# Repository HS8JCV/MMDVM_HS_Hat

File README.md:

# MMDVM_HS_Hat (VHF)
MMDVM_HS Hat for the Raspberry Pi (Zero)

This project forked from https://github.com/mathisschmieder/MMDVM_HS_Hat

This project provides a Raspberry Pi Hat for the [MMDVM_HS Hotspot](https://github.com/juribeparada/MMDVM_HS). It was designed for the Raspberry Pi Zero, but should work on any other Pi with the Hat interface. 

The PCB is designed in KiCad and the necessary libraries are included. The supplied Gerber files can be used to order PCBs, for example at Elecrow or DirtyPCBs. The board's dimensions are 65x30mm.

You can order 3 beautiful, purple Revision 1.2.1(VHF) PCBs for $15 at [OSHPark](https://oshpark.com/shared_projects/D5eErGib)! 

## Revisions
If you want to know about other revisions ,Please goto  orginal repository https://github.com/mathisschmieder/MMDVM_HS_Hat
### Revision 1.2.1(VHF)
This Revision forked from revision 1.2 of https://github.com/mathisschmieder/MMDVM_HS_Hat

Detail
- Remove ceramic UHF antenna
- Add Inductor for External VCO
- Changed resistor and capacitor loop filter value
- Changed Lowpass filter circuit and value

## Customize schematic with Simulation Software

## Spectrum Result
Agilent N9340B with 20dB Attenuator

Spurious(2nd Harmonic)

50Khz Span

## BOM
* All necessary parts for the Revision 1.2.1(VHF) board can be ordered at Mouser using the following [Shopping](https://www.mouser.com/ProjectManager/ProjectDetail.aspx?AccessID=52a714bcd7)

Either the ADF7021 or the ADF7021-N can be used. Define the proper version in the firmware!

## Firmware Installation
For specific details about the firmware installation, check [these](https://github.com/juribeparada/MMDVM_HS#build-de-firmware-and-upload-to-zumspot-rpi) instructions. The process is similar to the installation on the ZumSpot Pi. 

Enable the following settings in Config.h:

    #define MMDVM_HS_HAT_REV12
    #define ENABLE_ADF7021
    #define ADF7021_14_7456
    #define STM32_USART1_HOST
    #define ENABLE_SCAN_MODE

Build the firmware:

    make

And finally upload the firmware to the MMDVM_HS_Hat:

    sudo make mmdvm_hs_hat

## License
This project is released under the Creative Commons Attribution-NonCommercial-ShareAlike 3.0 (CC-BY-NC-SA 3.0, https://creativecommons.org/licenses/by-nc-sa/3.0/) license. You may edit and share it as you like, as long as credit is given and the license is not changed. You can build as many boards for you and your friends as you like and you can even sell it to them to cover your costs, **however it is strictly forbidden to turn this into a commercial product! You are not allowed to build and sell these boards for profit!**

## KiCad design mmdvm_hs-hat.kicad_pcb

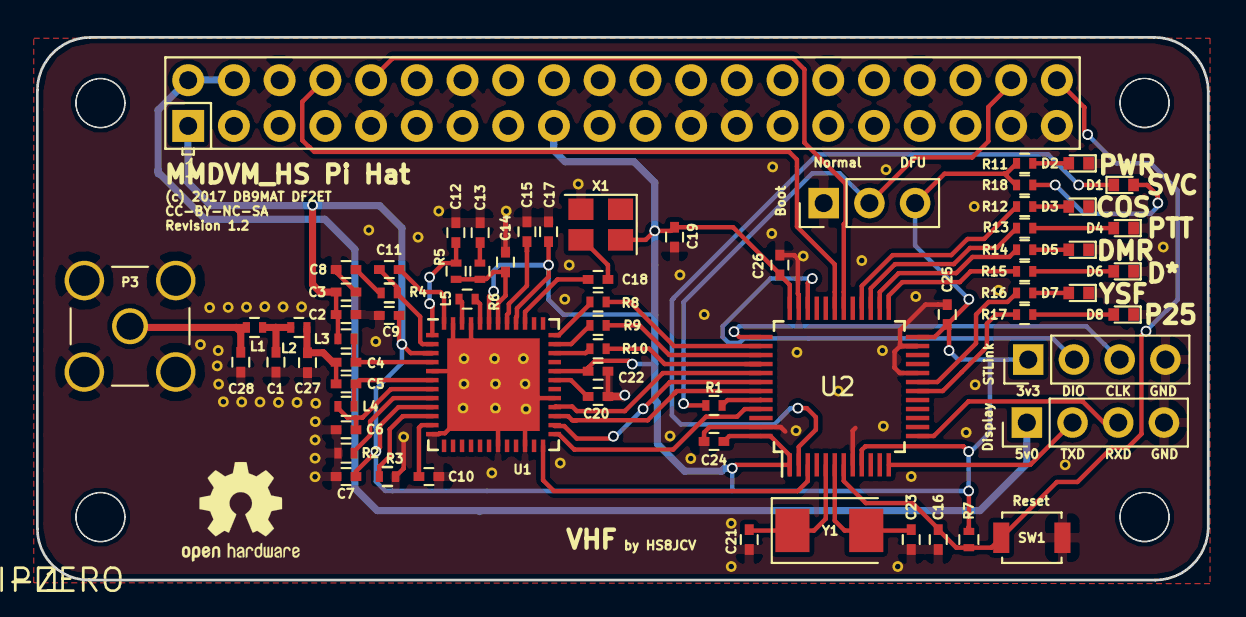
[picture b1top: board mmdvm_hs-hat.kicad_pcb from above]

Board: 2 copper layers, 65.1 x 30.2 mm, 69 parts (0 on the bottom side), 61 nets.

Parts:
C1, C27, C28: 15p; C_0402
C2, C7, C9, C17, C19, C22: 10n; C_0402
C3: 220p; C_0402
C4: 18p; C_0402
C5: 12p; C_0402
C6: 10p; C_0402
C8, C10, C15, C16, C20, C24, C25, C26: 100n; C_0402
C11: 22n; C_0402
C12: 82p; C_0402
C13: 2.7n; C_0402
C14: 200p; C_0402
C18: 22p; C_0402
C21, C23: 20p; C_0402
D1, D4, D8: red; LED_0402
D2, D6: green; LED_0402
D3, D5: yellow; LED_0402
D7: amber; LED_0402
L1: 150n; R_0402
L2: 130n; R_0402
L3: 100n; R_0402
L4: 200n; R_0402
L5: 20n; R_0402
P1: BOOT0; Pin_Header_Straight_1x03_Pitch2.54mm
P2: DISPLAY; Pin_Header_Straight_1x04_Pitch2.54mm
P3: SMA; SMA_THT_Jack_Straight
P4: STLINK; Pin_Header_Straight_1x04_Pitch2.54mm
PI1: RPI-ZERO; RPI-Zero-RASPBERRYPI_BASTELSTUBE_V13_RASPI_BOARD_B+_FULL
R1, R7: 10k; R_0402
R2: 1k1; R_0402
R3: 3k6; R_0402
R4: 2r; R_0402
R5: 3.4K; R_0402
R6: 1.65K; R_0402
R8, R9, R10, R11, R12, R13, R14, R15, R16, R17, R18: 1k; R_0402
SW1: SW_DIP_x01; SW_SPST_B3U-1000P
U1: ADF7021; QFN-48-1EP_7x7mm_Pitch0.5mm
U2: STM32F103C8T6; LQFP-48_7x7mm_Pitch0.5mm
X1: TCXO; Crystal_SMD_3225-4pin_3.2x2.5mm
Y1: 8MHz; Crystal_SMD_Abracon_ABM3-2pin_5.0x3.2mm

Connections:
+3V3: C2.1, C3.1, C7.1, C9.1, C17.1, C19.1, C22.2, C24.1, C25.1, C26.1, L3.2, P1.3, P4.1, PI1.1, PI1.17, R7.2, R11.2, R18.1, U1.3, U1.9, U1.32, U1.40, U1.43, U2.1, U2.9, U2.24, U2.36, U2.48, X1.4
+5V: P2.1, PI1.2, PI1.4
BOOT0: R1.1, U2.44
BOOT_GPIO: P1.2, PI1.38, R1.2
CE: U1.24, U2.3
CLKOUT: R8.1, U2.38
COS_LED: R12.2, U2.28
DATAIN: R9.1, U2.39
DATAOUT: R10.1, U2.40
DISP_RXD: P2.3, U2.13
DISP_TXD: P2.2, U2.12
DMR_LED: R14.2, U2.26
DSTAR_LED: R15.2, U2.25
GND: C1.2, C2.2, C3.2, C6.2, C7.2, C8.2, C9.2, C10.2, C12.2, C13.2, C14.2, C15.1, C16.2, C17.2, C19.2, C20.1, C21.1, C22.1, C23.1, C24.2, C25.2, C26.2, C27.2, C28.2, D2.1, D3.1, D4.1, D5.1, D6.1, D7.1, D8.1, P1.1, P2.4, P3.2, P4.4, PI1.6, PI1.9, PI1.14, PI1.20, PI1.23, PI1.25, PI1.30, PI1.34, PI1.37, PI1.39, R2.2, R3.2, SW1.2, U1.5, U1.12, U1.19, U1.22, U1.29, U1.45, U1.47, U1.49, U2.8, U2.20, U2.23, U2.35, U2.47, X1.2
NRST: C16.1, PI1.40, R7.1, SW1.1, U2.7
unnamed: C1.1, L1.2, L2.1
unnamed: C4.1, L3.1, U1.4
unnamed: C5.1, L4.2, U1.6
unnamed: C6.1, L4.1, U1.7
unnamed: C8.1, R4.2
unnamed: C10.1, U1.11
unnamed: C11.1, U1.48
unnamed: C11.2, R4.1, U1.2
unnamed: C12.1, R5.2, U1.1
unnamed: C13.1, R6.2
unnamed: C14.1, R5.1, R6.1, U1.42
unnamed: C15.2, U1.41
unnamed: C18.1, X1.3
unnamed: C18.2, U1.39
unnamed: C20.2, U1.31
unnamed: C21.2, U2.5, Y1.1
unnamed: C23.2, U2.6, Y1.2
unnamed: C4.2, C5.2, C27.1, L2.2
unnamed: C28.1, L1.1, P3.1
unnamed: D1.2, R18.2
unnamed: D2.2, R11.1
unnamed: D3.2, R12.1
unnamed: D4.2, R13.1
unnamed: D5.2, R14.1
unnamed: D6.2, R15.1
unnamed: D7.2, R16.1
unnamed: D8.2, R17.1
unnamed: L5.1, U1.46
unnamed: L5.2, U1.44
unnamed: R2.1, U1.8
unnamed: R3.1, U1.10
unnamed: R8.2, U1.36
unnamed: R9.2, U1.35
unnamed: R10.2, U1.34
P25_LED: R17.2, U2.18
PTT_LED: R13.2, U2.27
RXD: PI1.8, U2.31
SCLK: U1.28, U2.41
SDATA: U1.26, U2.42
SERVICE: D1.1, U2.2
SLE: U1.25, U2.45
SREAD: U1.27, U2.43
SWCLK: P4.3, U2.37
SWDIO: P4.2, U2.34
TXD: PI1.10, U2.30
YSF_LED: R16.2, U2.19

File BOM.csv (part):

Reference, Value, Footprint, Datasheet, MFR, MPN, SPR, SPN
"U2","STM32F103C8T6","Housings_QFP:LQFP-48_7x7mm_Pitch0.5mm","http://www.mouser.com/ds/2/389/stm32f103c8-956229.pdf","STMicroelectronics","STM32F103C8T6","Mouser","511-STM32F103C8T6"
"Y1","8MHz","Crystals:Crystal_SMD_Abracon_ABM3-2pin_5.0x3.2mm","http://www.mouser.com/ds/2/3/abm3-47699.pdf","ABRACON","ABM3-8.000MHz-D2Y-T","Mouser","815-ABM3-8-D2Y-T"
"C21","20p","Capacitors_SMD:C_0402","http://www.mouser.com/ds/2/281/c02e-2905.pdf","Murata Electronics","GJM1555C1H200FB01D","Mouser","81-GJM1555C1H200FB1D"
"C23","20p","Capacitors_SMD:C_0402","http://www.mouser.com/ds/2/281/c02e-2905.pdf","Murata Electronics","GJM1555C1H200FB01D","Mouser","81-GJM1555C1H200FB1D"
"P1","BOOT0","Pin_Headers:Pin_Header_Straight_1x03_Pitch2.54mm","http://www.mouser.com/ds/2/418/NG_CD_826629_AA_baseFilename-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","TE Connectivity / AMP","826629-3","Mouser","571-826629-3"
"P4","STLINK","Pin_Headers:Pin_Header_Straight_1x04_Pitch2.54mm","http://www.mouser.com/ds/2/418/NG_CD_826629_AA_baseFilename-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","TE Connectivity / AMP","826629-4","Mouser","571-826629-4"
"C24","100n","Capacitors_SMD:C_0402","http://www.mouser.com/ds/2/281/c03e-806517.pdf","Murata Electronics","GCM155R71C104JA55D","Mouser","81-GCM155R71C104JA5D"
"C25","100n","Capacitors_SMD:C_0402","http://www.mouser.com/ds/2/281/c03e-806517.pdf","Murata Electronics","GCM155R71C104JA55D","Mouser","81-GCM155R71C104JA5D"
"C26","100n","Capacitors_SMD:C_0402","http://www.mouser.com/ds/2/281/c03e-806517.pdf","Murata Electronics","GCM155R71C104JA55D","Mouser","81-GCM155R71C104JA5D"
"R1","10k","Resistors_SMD:R_0402","http://www.mouser.com/ds/2/427/dcrcwe3-109170.pdf","Vishay","CRCW040210K0FKED","Mouser","71-CRCW0402-10K-E3"
"R7","10k","Resistors_SMD:R_0402","http://www.mouser.com/ds/2/427/dcrcwe3-109170.pdf","Vishay","CRCW040210K0FKED","Mouser","71-CRCW0402-10K-E3"
"C16","100n","Capacitors_SMD:C_0402","http://www.mouser.com/ds/2/281/c03e-806517.pdf","Murata Electronics","GCM155R71C104JA55D","Mouser","81-GCM155R71C104JA5D"
"R8","1k","Resistors_SMD:R_0402","http://www.mouser.com/ds/2/315/AOA0000C291-1101061.pdf","Panasonic","ERJ-PA2D1001X","Mouser","667-ERJ-PA2D1001X"
"R9","1k","Resistors_SMD:R_0402","http://www.mouser.com/ds/2/315/AOA0000C291-1101061.pdf","Panasonic","ERJ-PA2D1001X","Mouser","667-ERJ-PA2D1001X"
"R10","1k","Resistors_SMD:R_0402","http://www.mouser.com/ds/2/315/AOA0000C291-1101061.pdf","Panasonic","ERJ-PA2D1001X","Mouser","667-ERJ-PA2D1001X"
"C20","100n","Capacitors_SMD:C_0402","http://www.mouser.com/ds/2/281/c03e-806517.pdf","Murata Electronics","GCM155R71C104JA55D","Mouser","81-GCM155R71C104JA5D"
"C22","10n","Capacitors_SMD:C_0402","http://www.mouser.com/ds/2/281/c02e-2905.pdf","Murata Electronics","GRM155R71H103KA88D","Mouser","81-GRM155R71H103KA8D"
"D2","green","LEDs:LED_0402","http://www.mouser.com/ds/2/348/sml-p1-471200.pdf","ROHM Semiconductor","SML-P13PTT86R","Mouser","755-SML-P13PTT86R"
"D3","yellow","LEDs:LED_0402","http://www.mouser.com/ds/2/348/sml-p1-471200.pdf","ROHM Semiconductor","SML-P12WTT86R","Mouser","755-SML-P12WTT86R"
"D4","red","LEDs:LED_0402","http://www.mouser.com/ds/2/348/sml-p1-471200.pdf","ROHM Semiconductor","SML-P12U2TT86R","Mouser","755-SML-P12U2TT86R"
"D5","yellow","LEDs:LED_0402","http://www.mouser.com/ds/2/348/sml-p1-471200.pdf","ROHM Semiconductor","SML-P12WTT86R","Mouser","755-SML-P12WTT86R"
"D6","green","LEDs:LED_0402","http://www.mouser.com/ds/2/348/sml-p1-471200.pdf","ROHM Semiconductor","SML-P13PTT86R","Mouser","755-SML-P13PTT86R"
"D7","amber","LEDs:LED_0402","http://www.mouser.com/ds/2/348/sml-p1-471200.pdf","ROHM Semiconductor","SML-P12DTT86R","Mouser","755-SML-P12DTT86R"
"D8","red","LEDs:LED_0402","http://www.mouser.com/ds/2/348/sml-p1-471200.pdf","ROHM Semiconductor","SML-P12U2TT86R","Mouser","755-SML-P12U2TT86R"
"R11","1k","Resistors_SMD:R_0402","http://www.mouser.com/ds/2/315/AOA0000C291-1101061.pdf","Panasonic","ERJ-PA2D1001X","Mouser","667-ERJ-PA2D1001X"
"R12","1k","Resistors_SMD:R_0402","http://www.mouser.com/ds/2/315/AOA0000C291-1101061.pdf","Panasonic","ERJ-PA2D1001X","Mouser","667-ERJ-PA2D1001X"
"R13","1k","Resistors_SMD:R_0402","http://www.mouser.com/ds/2/315/AOA0000C291-1101061.pdf","Panasonic","ERJ-PA2D1001X","Mouser","667-ERJ-PA2D1001X"
"R14","1k","Resistors_SMD:R_0402","http://www.mouser.com/ds/2/315/AOA0000C291-1101061.pdf","Panasonic","ERJ-PA2D1001X","Mouser","667-ERJ-PA2D1001X"
"R15","1k","Resistors_SMD:R_0402","http://www.mouser.com/ds/2/315/AOA0000C291-1101061.pdf","Panasonic","ERJ-PA2D1001X","Mouser","667-ERJ-PA2D1001X"
"R16","1k","Resistors_SMD:R_0402","http://www.mouser.com/ds/2/315/AOA0000C291-1101061.pdf","Panasonic","ERJ-PA2D1001X","Mouser","667-ERJ-PA2D1001X"
"R17","1k","Resistors_SMD:R_0402","http://www.mouser.com/ds/2/315/AOA0000C291-1101061.pdf","Panasonic","ERJ-PA2D1001X","Mouser","667-ERJ-PA2D1001X"
"C10","100n","Capacitors_SMD:C_0402","http://www.mouser.com/ds/2/281/c03e-806517.pdf","Murata Electronics","GCM155R71C104JA55D","Mouser","81-GCM155R71C104JA5D"
"R3","3k6","Resistors_SMD:R_0402","http://www.mouser.com/ds/2/315/AOA0000C307-1149632.pdf","Panasonic","ERA-2AEB362X","Mouser","667-ERA-2AEB362X"
"C7","10n","Capacitors_SMD:C_0402","http://www.mouser.com/ds/2/281/c02e-2905.pdf","Murata Electronics","GRM155R71H103KA88D","Mouser","81-GRM155R71H103KA8D"
"R2","1k1","Resistors_SMD:R_0402","http://www.mouser.com/ds/2/392/susumu_RR_Data_Sheet-358748.pdf","Susumu","RR0510P-112-D","Mouser","754-RR0510P-112D"
"U1","ADF7021","Housings_DFN_QFN:QFN-48-1EP_7x7mm_Pitch0.5mm","http://www.mouser.com/ds/2/609/ADF7021-878461.pdf","Analog Devices","ADF7021BCPZ","Mouser","584-ADF7021BCPZ"
"C6","10p","Capacitors_SMD:C_0402","http://www.mouser.com/ds/2/281/c02e-2905.pdf","Murata Electronics","GJM1555C1H6R8BB01D","Mouser","81-GJM1555C1H6R8BB1D"
"L4","200n","Resistors_SMD:R_0402","http://www.mouser.com/ds/2/597/0402af-270718.pdf","Coilcraft","0402AF-201XJLU","Mouser","994-0402AF-201XJLU"
"C5","12p","Capacitors_SMD:C_0402","http://www.mouser.com/ds/2/281/c02e-2905.pdf","Murata Electronics","GRM1555C1H120FA1D","Mouser","81-GRM1555C1H120FA1D"
"C4","18p","Capacitors_SMD:C_0402","http://www.mouser.com/ds/2/281/c02e-2905.pdf","Murata Electronics","GRM1555C1H180JA1D","Mouser","81-GRM1555C1H180JA1D"
"L2","130n","Resistors_SMD:R_0402","http://www.mouser.com/ds/2/400/nductor_commercial_high-frequ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","TDK","MLG1005SR13JTD25","Mouser","810-MLG1005SR13JTD25"
"L1","150n","Resistors_SMD:R_0402","http://www.mouser.com/ds/2/400/nductor_commercial_high-frequ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","TDK","MLG1005SR15JTD25","Mouser","810-MLG1005SR15JTD25"
"L3","100n","Resistors_SMD:R_0402","http://www.mouser.com/ds/2/597/0402hp-270660.pdf","Coilcraft","0402HPH-R10XJLW","Mouser","994-0402HPH-R10XJLW"
"C3","220p","Capacitors_SMD:C_0402","http://www.mouser.com/ds/2/281/c02e-2905.pdf","Murata Electronics","GRM1555C1H221JA01D","Mouser","81-GRM1555C1H221JA01"
"C9","10n","Capacitors_SMD:C_0402","http://www.mouser.com/ds/2/281/c02e-2905.pdf","Murata Electronics","GRM155R71H103KA88D","Mouser","81-GRM155R71H103KA8D"
"C11","22n","Capacitors_SMD:C_0402","http://www.mouser.com/ds/2/281/c03e-806517.pdf","Murata Electronics","GCM155R71E223KA55D","Mouser","81-GCM155R71E223KA5D"
"R4","2r","Resistors_SMD:R_0402","http://www.mouser.com/ds/2/427/dcrcwe3-109170.pdf","Vishay","CRCW04022R00FKED","Mouser","71-CRCW0402-2-E3"
"C8","100n","Capacitors_SMD:C_0402","http://www.mouser.com/ds/2/281/c03e-806517.pdf","Murata Electronics","GCM155R71C104JA55D","Mouser","81-GCM155R71C104JA5D"
"C2","10n","Capacitors_SMD:C_0402","http://www.mouser.com/ds/2/281/c02e-2905.pdf","Murata Electronics","GRM155R71H103KA88D","Mouser","81-GRM155R71H103KA8D"
"R5","3.4K","Resistors_SMD:R_0402","http://www.mouser.com/ds/2/315/AOA0000C307-1149632.pdf","Panasonic","ERA-2AEB3401X","Mouser","667-ERA-2AEB3401X"
"R6","1.65K","Resistors_SMD:R_0402","http://www.mouser.com/ds/2/315/AOA0000C307-1149632.pdf","Panasonic","ERA-2AEB1651X","Mouser","667-ERA-2AEB1651X"
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
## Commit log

2017-10-18 The commit of MMDVM Hat VHF project
2017-10-19 Add VHF simulation result
2017-10-19 Add new BOM for VHF
2017-10-19 remove BOM.xlsx
2017-10-19 Edited schematic for VHF
2017-10-19 3D imgae of VHF version
2017-10-19 Added detail of VHF version
2017-10-19 Last VHF gerber files
2017-11-14 Added simulation detail of VHF version
2017-12-11 Add spectrum result
2017-12-11 Edited for last BOM
2017-12-11 Spectum result
2017-12-11 add mouser shopping cart

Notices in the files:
mmdvm_hs-hat.kicad_pcb:
(c) 2017 DB9MAT DF2ET
CC-BY-NC-SA
